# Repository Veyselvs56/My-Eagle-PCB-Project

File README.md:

This marks the beginning of my work in embedded systems and PCB design.

Image of the board section

Image of the schematic section

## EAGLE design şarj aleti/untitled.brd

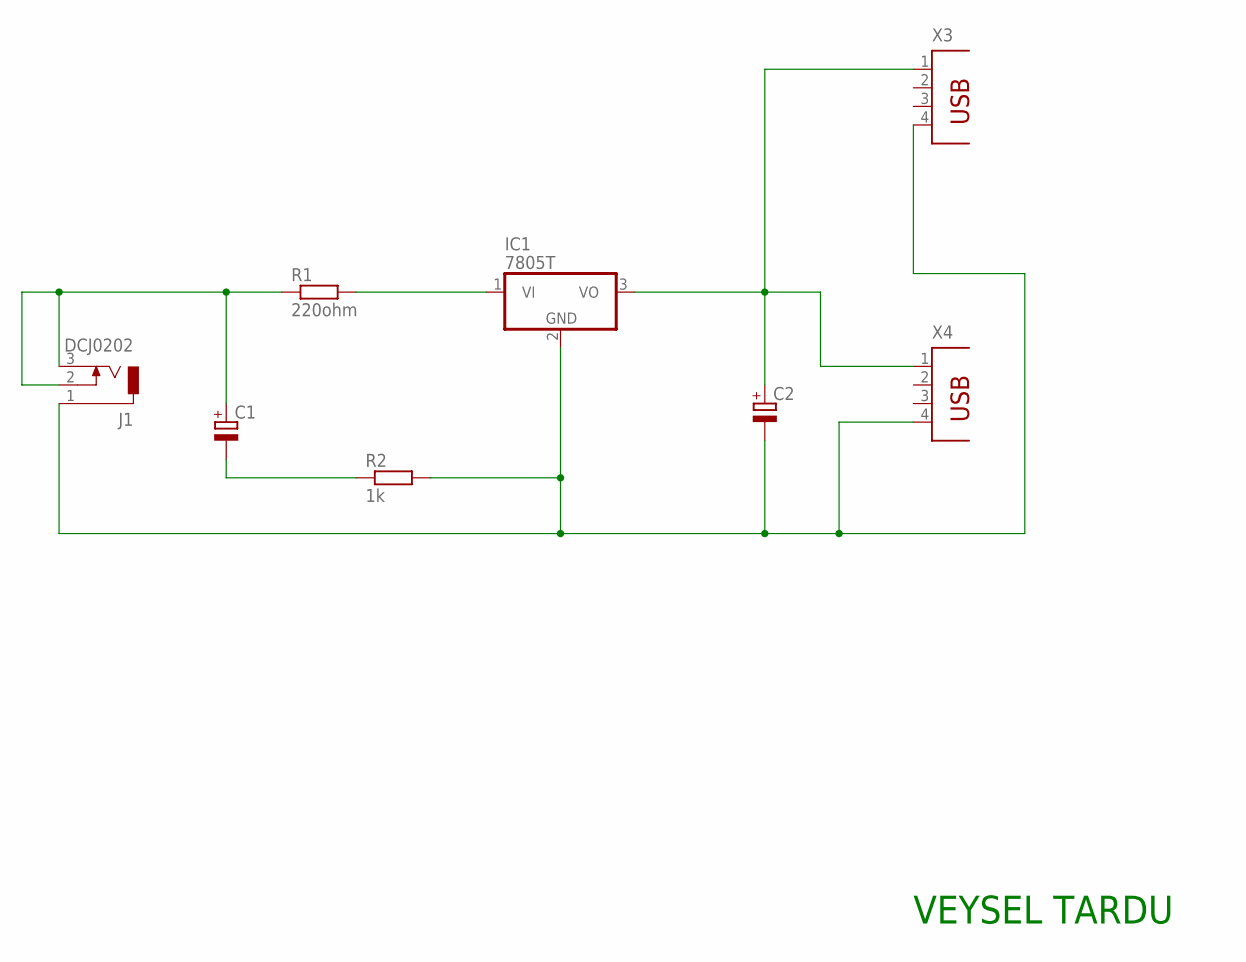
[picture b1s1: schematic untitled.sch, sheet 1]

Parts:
C1, C2: CPOL-EUE2-5; E2-5
IC1: 7805T; TO220H
J1: DCJ0202
R1: 220ohm; VMTA55
R2: 1k; VMTA55
X3, X4: PN61729

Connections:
unnamed: C1.+, J1.2, J1.3, R1.1
unnamed: IC1.1 (VI), R1.2
unnamed: C2.-, IC1.2 (GND), J1.1, R2.2, X3.4, X4.4
unnamed: C2.+, IC1.3 (VO), X3.1, X4.1
unnamed: C1.-, R2.1

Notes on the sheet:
VEYSEL TARDU

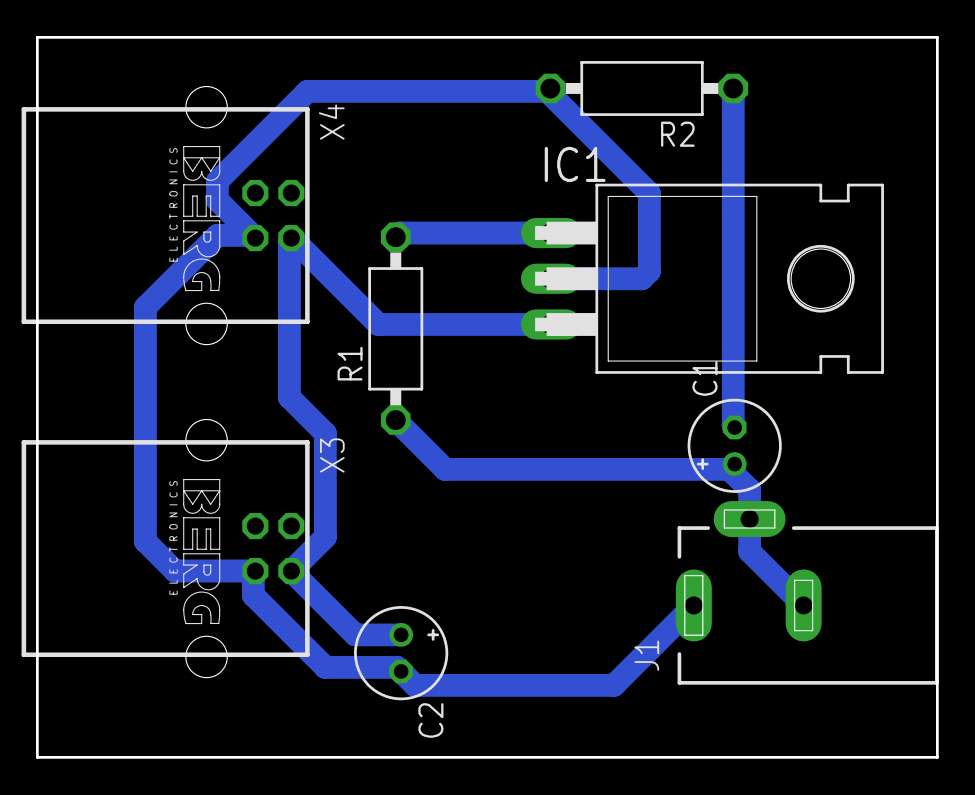
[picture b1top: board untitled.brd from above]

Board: 2 copper layers, 50.0 x 40.0 mm, 8 parts (0 on the bottom side), 5 nets.

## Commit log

2025-04-30 My eagle PCB Project
